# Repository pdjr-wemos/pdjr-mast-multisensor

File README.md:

# pdjr-mast-multisensor

This project implements an
[ESP8266](https://www.espressif.com/en/products/socs/esp8266)-based
multisensor which mounts at the top of
[Beatrice](https://www.pdjr.eu/beatrice/wp-content/uploads/2021/01/beatrice.jpg)'s
mast and reports temperature, humidity, barometric pressure, lux and mast
state (raised/lowered).

The multisensor PCB is housed in a 3D printed enclosure which sits
between the mast top plate and the
[DHR35 Anchor Light](https://www.dhr.nl/dhr-marine/products/navigation-lights/dhr35).
The housing adds about 2cm to the mast height.

The PCB incorporates the following active components.

* [Wemos D1 Mini](https://www.wemos.cc/en/latest/d1/d1_mini.html)
* [Adafruit AM2320](https://www.adafruit.com/product/3721) temperature + humidity sensor
* [Bosch BMP581](https://www.bosch-sensortec.com/products/environmental-sensors/pressure-sensors/bmp581/) temperature + barometric pressure sensor
* [SW-520D](https://www.switchelectronics.co.uk/products/sw520d-ball-tilt-vibration-switch) tilt sensor
* [VEML7700](https://www.vishay.com/docs/84286/veml7700.pdf) lux sensor

The multisensor is configured and provisioned using
[ESPHome](https://esphome.io/index.html),
connects to the ships's WiFi network and integrates with the vessel's
[Home Assistant](https://www.home-assistant.io/)
platform.

<table>
  <tr>
    <td>
           
    </td>
    <td>
      
    </td>
  </tr>
</table>

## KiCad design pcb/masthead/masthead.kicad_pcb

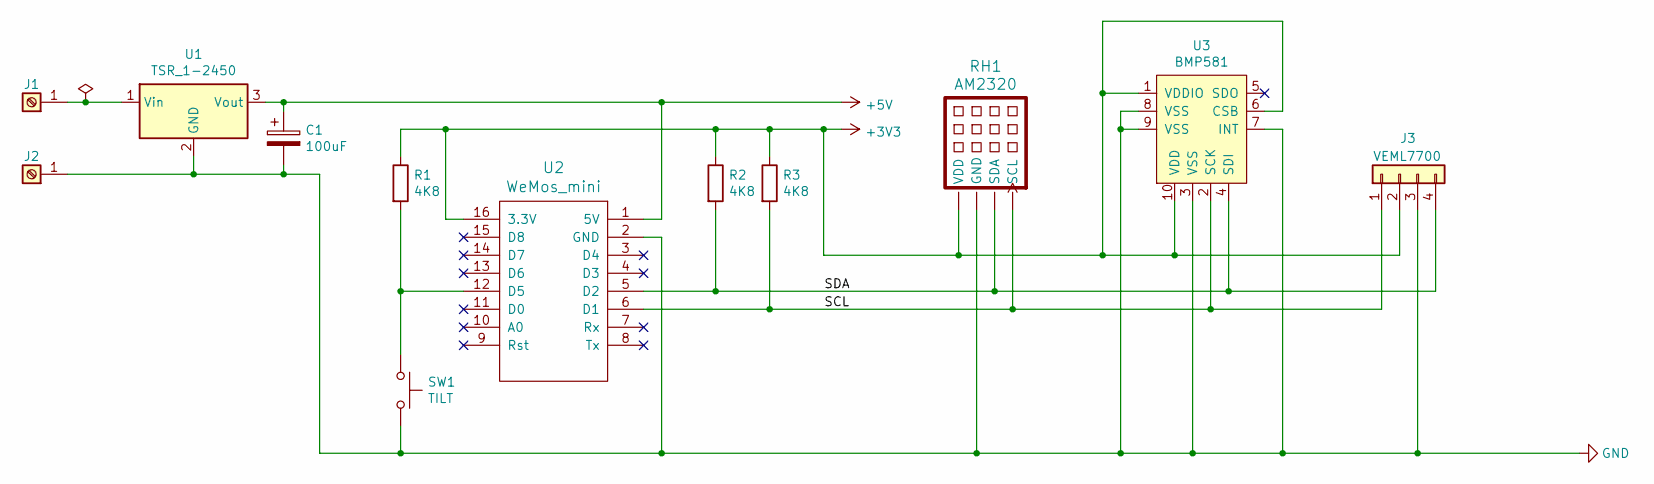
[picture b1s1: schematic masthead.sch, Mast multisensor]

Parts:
C1: 100uF; CP_Radial_D6.3mm_P2.50mm
J1, J2: Open screw terminal 5x7; M4_OPEN_TERMINAL
J3: VEML7700; VEML7700_SIDE
R1, R2, R3: 4K8; R_1206_3216Metric_Pad1.30x1.75mm_HandSolder
RH1: AM2320; AM2320_HORIZ
SW1: TILT; PinSocket_1x02_P2.54mm_Vertical
U1: TSR_1-2450; Converter_DCDC_TRACO_TSR-1_THT
U2: WeMos_mini; Wemos_D1_mini
U3: BMP581

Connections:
+3V3: J3.2, R1.1, R2.1, R3.1, RH1.1 (VDD), U2.16 (3.3V), U3.1 (VDDIO), U3.6 (CSB), U3.10 (VDD)
+5V: C1.1, U1.3 (Vout), U2.1 (5V)
/SCL: J3.1, R3.2, RH1.4 (SCL), U2.6 (D1), U3.2 (SCK)
/SDA: J3.4, R2.2, RH1.2 (SDA), U2.5 (D2), U3.4 (SDI)
GND: C1.2, J2.1, J3.3, RH1.3 (GND), SW1.2, U1.2 (GND), U2.2 (GND), U3.3 (VSS), U3.7 (INT), U3.8 (VSS), U3.9 (VSS)
unnamed: J1.1, U1.1 (Vin)
unnamed: R1.2, SW1.1, U2.12 (D5)

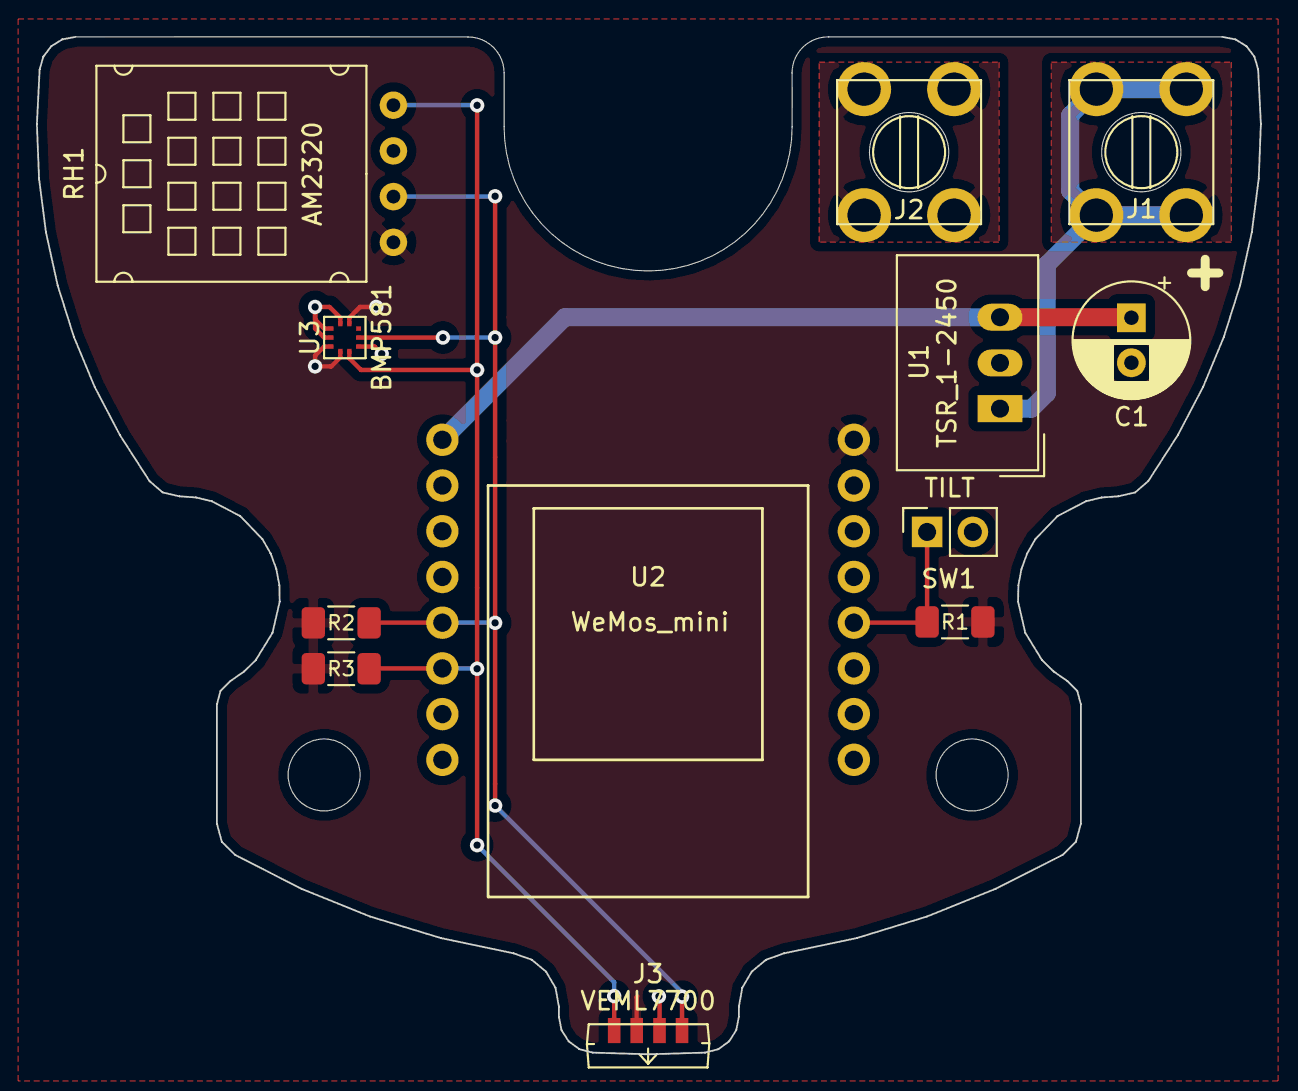
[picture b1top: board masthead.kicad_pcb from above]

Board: 2 copper layers, 68.0 x 56.5 mm, 12 parts (1 on the bottom side), 7 nets.

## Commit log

2024-01-30 First upload
2024-01-31 Tweaks
2024-01-31 Tweak
2024-02-01 Finalise
2024-02-01 Deleted .DS_Store
2024-02-01 Add gcode
2024-02-01 Add stl
2024-02-02 PCB tweak
2024-02-04 Add VEML7700
2024-02-06 New version of enclosure
